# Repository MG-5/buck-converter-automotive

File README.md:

# buck-converter-automotive
12V to 5V 1A buck converter to automotive purposes

### Requirements for rev 1.0
* efficient step-down synchronous converter
* fuse
* TVS diodes
* reverse polarity protection
* LC input filter
* power-on LED

### Pictures (rev 1.0)

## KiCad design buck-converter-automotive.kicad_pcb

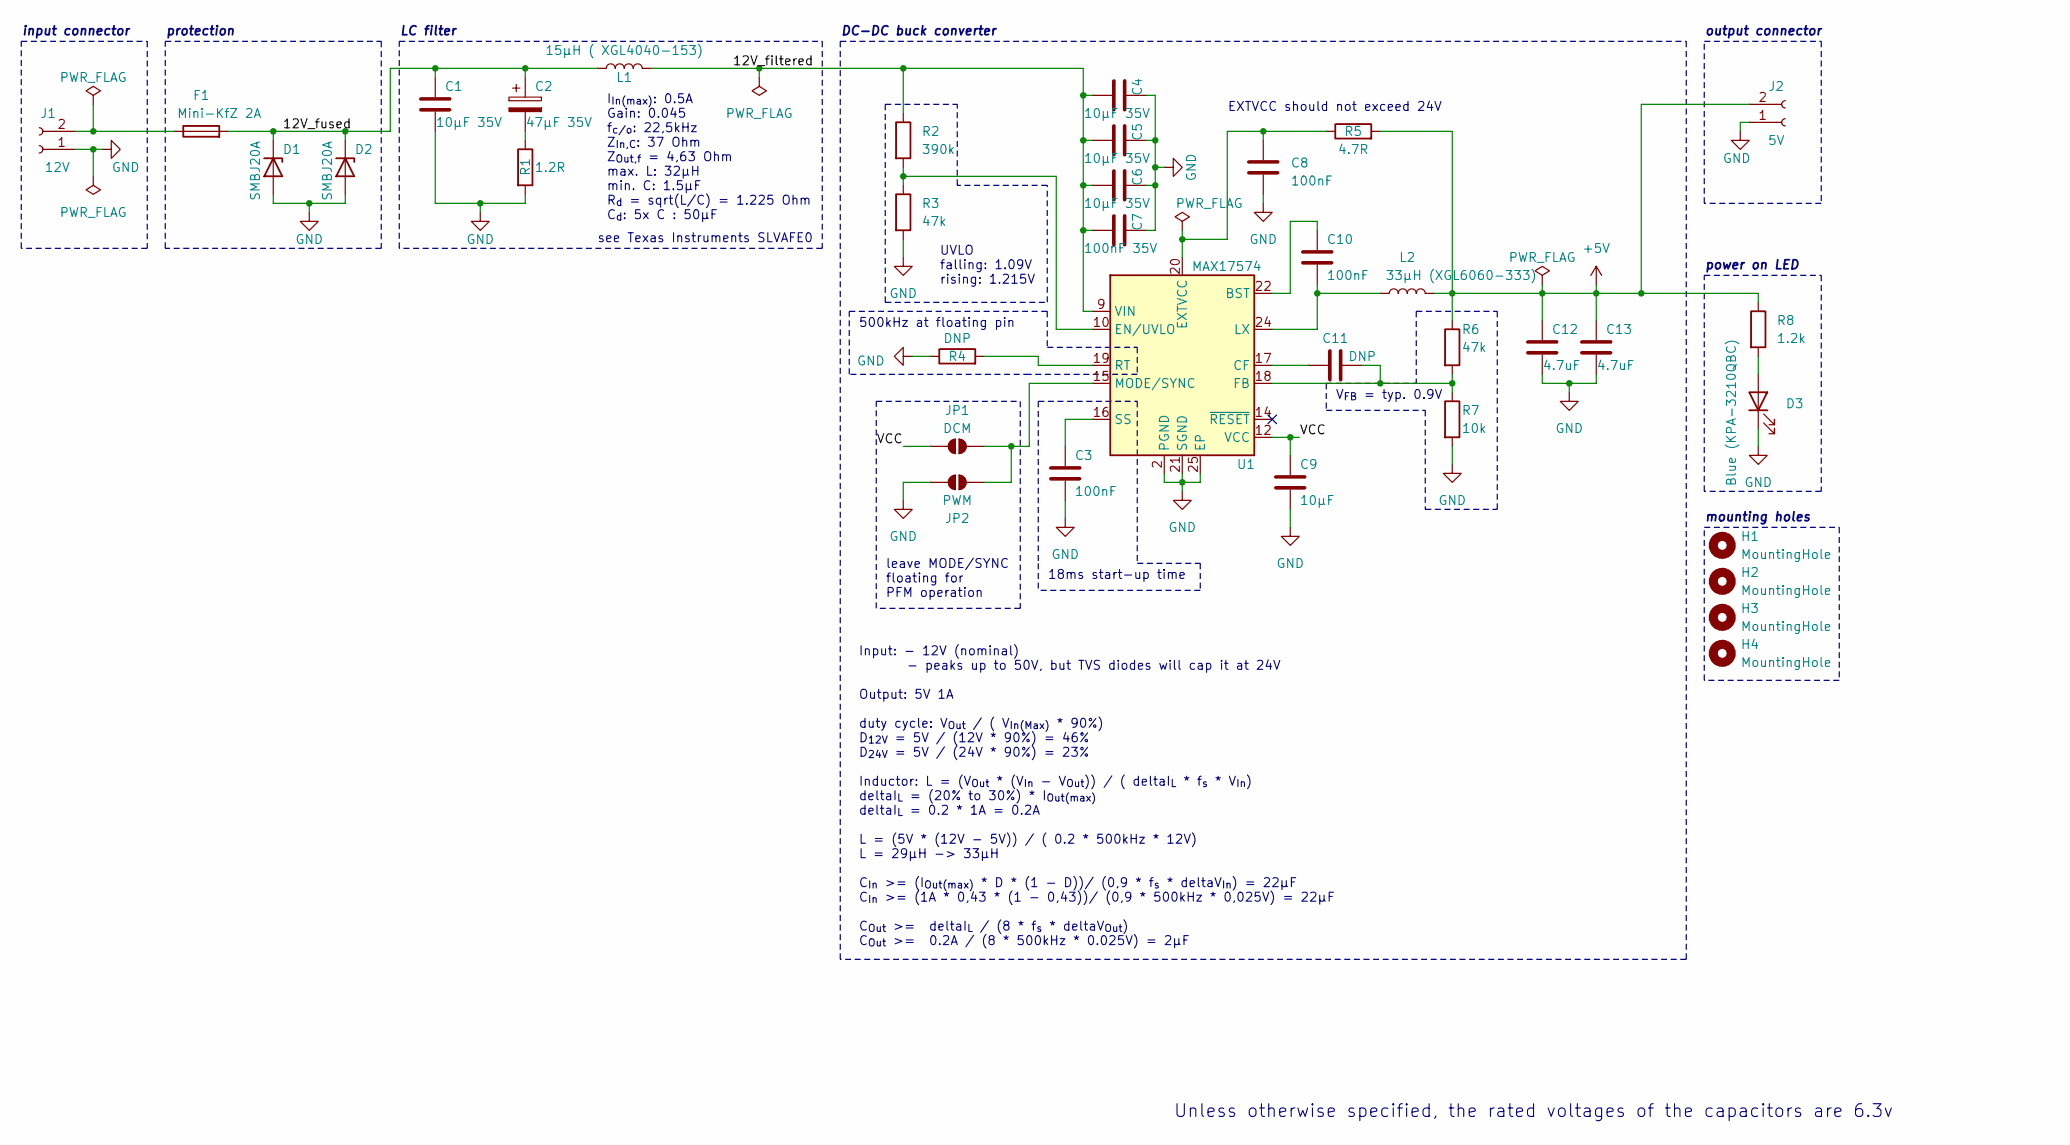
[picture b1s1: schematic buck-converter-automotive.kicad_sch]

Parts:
C1, C4, C5, C6: 10µF 35V; C_0603_1608Metric_Pad1.08x0.95mm_HandSolder
C2: 47µF 35V; C_Elec_6.3x5.8
C3, C8, C10: 100nF; C_0603_1608Metric_Pad1.08x0.95mm_HandSolder
C7: 100nF 35V; C_0603_1608Metric_Pad1.08x0.95mm_HandSolder
C9: 10µF; C_0805_2012Metric_Pad1.18x1.45mm_HandSolder
C11: DNP; C_0603_1608Metric_Pad1.08x0.95mm_HandSolder
C12, C13: 4.7uF; C_0603_1608Metric_Pad1.08x0.95mm_HandSolder
D1, D2: SMBJ20A; D_SMB_Handsoldering
D3: Blue (KPA-3210QBC); LED_1206_3216Metric
F1: Mini-KfZ 2A; KEYSTONE-FUSE-3557-2
H1, H2, H3, H4: MountingHole; MountingHole_3.2mm_M3_ISO14580
J1: 12V; Molex_PicoBlade_53047-0210_1x02_P1.25mm_Vertical
J2: 5V; Molex_PicoBlade_53047-0210_1x02_P1.25mm_Vertical
JP1: DCM; SolderJumper-Open_0603
JP2: PWM; SolderJumper-Open_0603
L1: 15µH ( XGL4040-153); L_Coilcraft_XAL4040-XXX
L2: 33µH (XGL6060-333); L_Coilcraft_XAL6060-XXX
R1: 1.2R; R_0603_1608Metric_Pad0.98x0.95mm_HandSolder
R2: 390k; R_0603_1608Metric_Pad0.98x0.95mm_HandSolder
R3, R6: 47k; R_0603_1608Metric_Pad0.98x0.95mm_HandSolder
R4: DNP; R_0603_1608Metric_Pad0.98x0.95mm_HandSolder
R5: 4.7R; R_0603_1608Metric_Pad0.98x0.95mm_HandSolder
R7: 10k; R_0603_1608Metric_Pad0.98x0.95mm_HandSolder
R8: 1.2k; R_0603_1608Metric_Pad0.98x0.95mm_HandSolder
U1: MAX17574; QFN-24-1EP_4x5mm_P0.5mm_EP2.65x3.65mm

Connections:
+5V: C12.2, C13.2, J2.2, L2.2, R5.2, R6.1, R8.1
/12V_filtered: C4.1, C5.1, C6.1, C7.1, L1.2, R2.1, U1.5 (VIN), U1.6 (VIN), U1.7 (VIN), U1.9 (VIN)
/12V_fused: C1.1, C2.1, D1.1 (K), D2.1 (K), F1.2, L1.1
/VCC: C9.1, JP1.1 (A), U1.12 (VCC)
GND: C1.2, C3.2, C4.2, C5.2, C6.2, C7.2, C8.1, C9.2, C12.1, C13.1, D1.2 (A), D2.2 (A), D3.1 (K), J1.1, J2.1, JP2.1 (A), R1.2, R3.2, R4.1, R7.2, U1.2 (PGND), U1.3 (PGND), U1.11 (PGND), U1.21 (SGND), U1.25 (EP)
unnamed: C2.2, R1.1
unnamed: C10.1, L2.1, U1.1 (LX), U1.23 (LX), U1.24 (LX)
unnamed: D3.2 (A), R8.2
unnamed: F1.1, J1.2
unnamed: JP1.2 (B), JP2.2 (B), U1.15 (MODE/SYNC)
unnamed: C10.2, U1.22 (BST)
unnamed: C11.1, U1.17 (CF)
unnamed: R2.2, R3.1, U1.10 (EN/UVLO)
unnamed: C8.2, R5.1, U1.20 (EXTVCC)
unnamed: C11.2, R6.2, R7.1, U1.18 (FB)
unnamed: R4.2, U1.19 (RT)
unnamed: C3.1, U1.16 (SS)

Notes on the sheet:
power on LED
DC-DC buck converter
leave MODE/SYNC floating for PFM operation
I_{In(max)}: 0.5A Gain: 0.045 f_{c/o}: 22,5kHz Z_{In,C}: 37 Ohm Z_{Out,f} = 4,63 Ohm max. L: 32µH min. C: 1.5µF R_{d} = sqrt(L/C) = 1.225 Ohm C_{d}: 5x C : 50µF
UVLO falling: 1.09V rising: 1.215V
LC filter
input connector
500kHz at floating pin
protection
Unless otherwise specified, the rated voltages of the capacitors are 6.3v
EXTVCC should not exceed 24V
see Texas Instruments SLVAFE0
18ms start-up time
Input: - 12V (nominal) - peaks up to 50V, but TVS diodes will cap it at 24V Output: 5V 1A duty cycle: V_{Out} / ( V_{In(Max)} * 90%) D_{12V} = 5V / (12V * 90%) = 46% D_{24V} = 5V / (24V * 90%) = 23% Inductor: L = (V_{Out} * (V_{In} - V_{Out})) / ( deltaI_{L} * f_{s} * V_{In}) deltaI_{L} = (20% to 3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
mounting holes
output connector
V_{FB} = typ. 0.9V

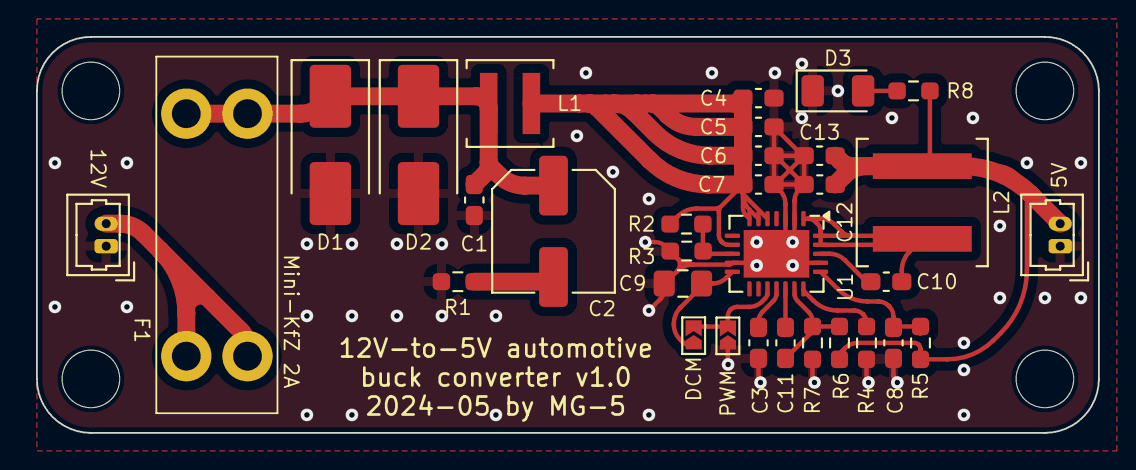
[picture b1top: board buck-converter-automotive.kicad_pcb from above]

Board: 2 copper layers, 59.0 x 22.0 mm, 36 parts (0 on the bottom side), 17 nets.

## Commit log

2024-05-25 Init project Add schematic Add PCB
2024-07-10 Make some parts as DNP
